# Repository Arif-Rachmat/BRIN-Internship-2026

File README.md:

<div align=center>
<table width="100%">
  <tr>
    <td width="25%" align="center">
      
    </td>
    <td width="50%" align="center">
      <h1>BRIN Internship - 2026</h1>
      <h3>Embedded Electronic Systems</h3>
    </td>
    <td width="25%"></td>
  </tr>
</table>

A collection of technical work, experiments, notes, and deliverables developed throughout my internship at **BRIN**.

</div>

---

## 🧭 Navigation

This repository is organized into individual workspaces assign to different branch, each containing the relevant implementation, documentation, experiments, and supporting files.

## Download / Cloning

To download or clone a specific branch, use this command:

```shell
git clone --branch=<branch-name> https://github.com/Arif-Rachmat/BRIN-Internship-2026.git <output-directory>
```

<!-- ASSIGNMENTS:START -->

### 📚 Index

1. Circuit/Electronics Design
   * [Basic #0: Adjustable Linear Power Supply](https://github.com/Arif-Rachmat/BRIN-Internship-2026/tree/Circuit-Basic-0-AdjLinearSupply)
   * [Intermediate #1: ATmega16–STM32BluePill Breakout/Adapter](https://github.com/Arif-Rachmat/BRIN-Internship-2026/tree/Circuit-Intermediate-1-ATmega16-STM32BP-Adapter)
   * [Capstone #0: Raspberry PI Dev Board](https://github.com/Arif-Rachmat/BRIN-Internship-2026/tree/Circuit-Capstone-0-RasPiDevBoard)
   * [Capstone #1: Tomography Switch Board Matrix](https://github.com/Arif-Rachmat/BRIN-Internship-2026/tree/Circuit-Capstone-1-TomographySwitchBoard)
     * [Capstone #1.1: TomographySwitchBoardV2](https://github.com/Arif-Rachmat/BRIN-Internship-2026/tree/Circuit-Capstone-1.1-TomographySwitchBoardV2main)
2. Embedded Programming
   * [Basic #0: Non-Blocking Blinky](https://github.com/Arif-Rachmat/BRIN-Internship-2026/tree/Embedded-Basic-0-NonBlocking-Blinky)
   * [Basic #1: UART](https://github.com/Arif-Rachmat/BRIN-Internship-2026/tree/Embedded-Basic-1-UART)
   * [Basic #2: ADC](https://github.com/Arif-Rachmat/BRIN-Internship-2026/tree/Embedded-Basic-2-ADC)
   * [Intermediate #1: I2C - LCD w/ PCF8574](https://github.com/Arif-Rachmat/BRIN-Internship-2026/tree/Circuit-Intermediate-1-I2C)
   * [Intermediate #3: 1-Wire DS18B20 Temperature Sensor](https://github.com/Arif-Rachmat/BRIN-Internship-2026/tree/Circuit-Intermediate-3-Onewire-DS18b20)

<!-- ASSIGNMENTS:END -->

---

<p align="center">
  <sub>Maintained as a personal technical workspace during my internship at BRIN.</sub>
</p>

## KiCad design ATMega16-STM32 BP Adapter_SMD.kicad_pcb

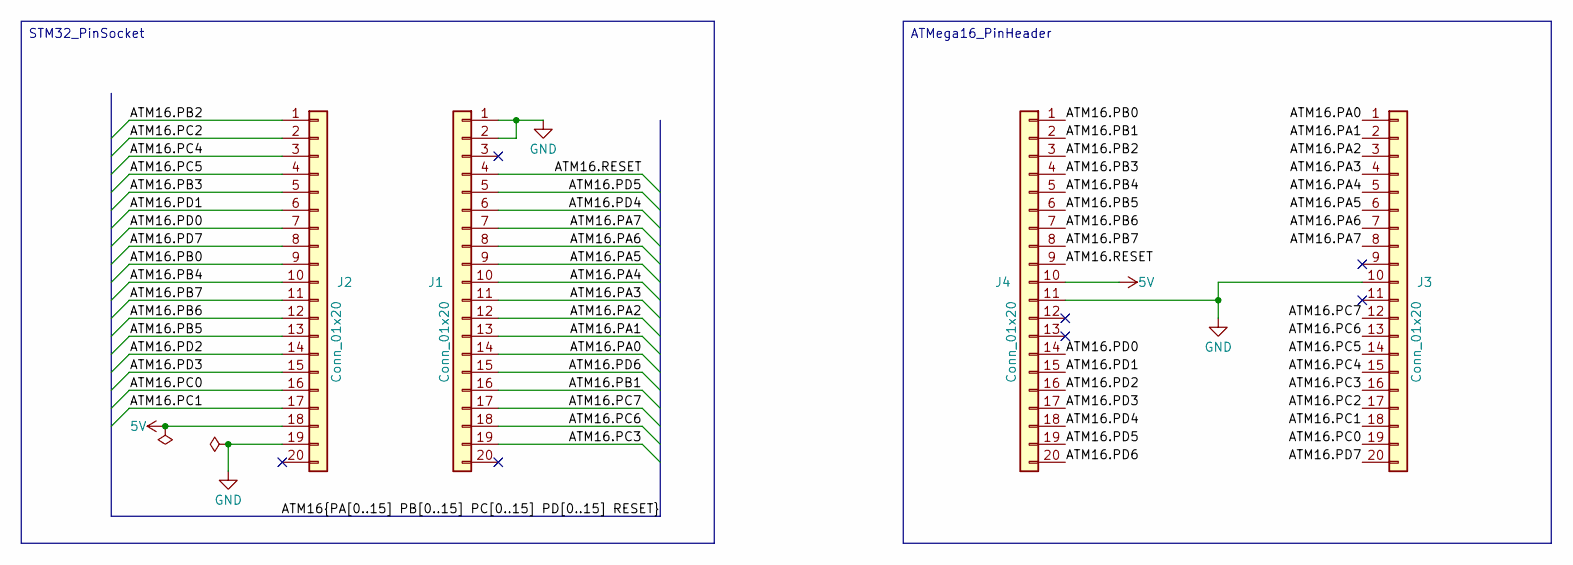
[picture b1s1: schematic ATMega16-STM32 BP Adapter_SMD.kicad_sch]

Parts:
J1: Conn_01x20; PinSocket_1x20_P2.54mm_Vertical_SMD_Pin1Right
J2: Conn_01x20; PinSocket_1x20_P2.54mm_Vertical_SMD_Pin1Left
J3: Conn_01x20; PinHeader_1x20_P2.54mm_Vertical_SMD_Pin1Right
J4: Conn_01x20; PinHeader_1x20_P2.54mm_Vertical_SMD_Pin1Left

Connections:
5V: J2.18, J4.10
/ATM16.PA0: J1.14, J3.1
/ATM16.PA1: J1.13, J3.2
/ATM16.PA2: J1.12, J3.3
/ATM16.PA3: J1.11, J3.4
/ATM16.PA4: J1.10, J3.5
/ATM16.PA5: J1.9, J3.6
/ATM16.PA6: J1.8, J3.7
/ATM16.PA7: J1.7, J3.8
/ATM16.PB0: J2.9, J4.1
/ATM16.PB1: J1.16, J4.2
/ATM16.PB2: J2.1, J4.3
/ATM16.PB3: J2.5, J4.4
/ATM16.PB4: J2.10, J4.5
/ATM16.PB5: J2.13, J4.6
/ATM16.PB6: J2.12, J4.7
/ATM16.PB7: J2.11, J4.8
/ATM16.PC0: J2.16, J3.19
/ATM16.PC1: J2.17, J3.18
/ATM16.PC2: J2.2, J3.17
/ATM16.PC3: J1.19, J3.16
/ATM16.PC4: J2.3, J3.15
/ATM16.PC5: J2.4, J3.14
/ATM16.PC6: J1.18, J3.13
/ATM16.PC7: J1.17, J3.12
/ATM16.PD0: J2.7, J4.14
/ATM16.PD1: J2.6, J4.15
/ATM16.PD2: J2.14, J4.16
/ATM16.PD3: J2.15, J4.17
/ATM16.PD4: J1.6, J4.18
/ATM16.PD5: J1.5, J4.19
/ATM16.PD6: J1.15, J4.20
/ATM16.PD7: J2.8, J3.20
/ATM16.RESET: J1.4, J4.9
GND: J1.1, J1.2, J2.19, J3.10, J4.11

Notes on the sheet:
ATMega16_PinHeader
STM32_PinSocket

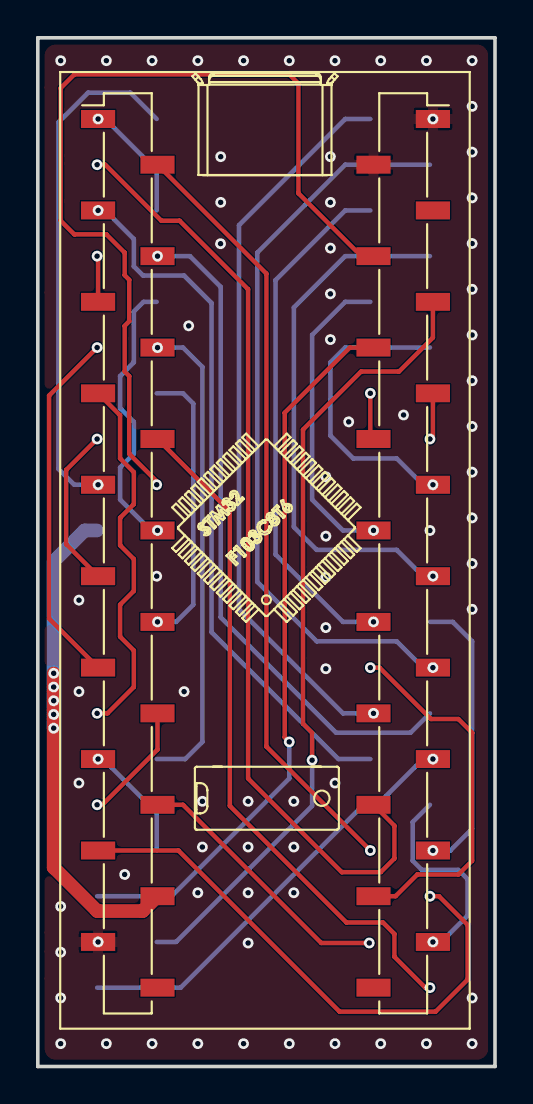
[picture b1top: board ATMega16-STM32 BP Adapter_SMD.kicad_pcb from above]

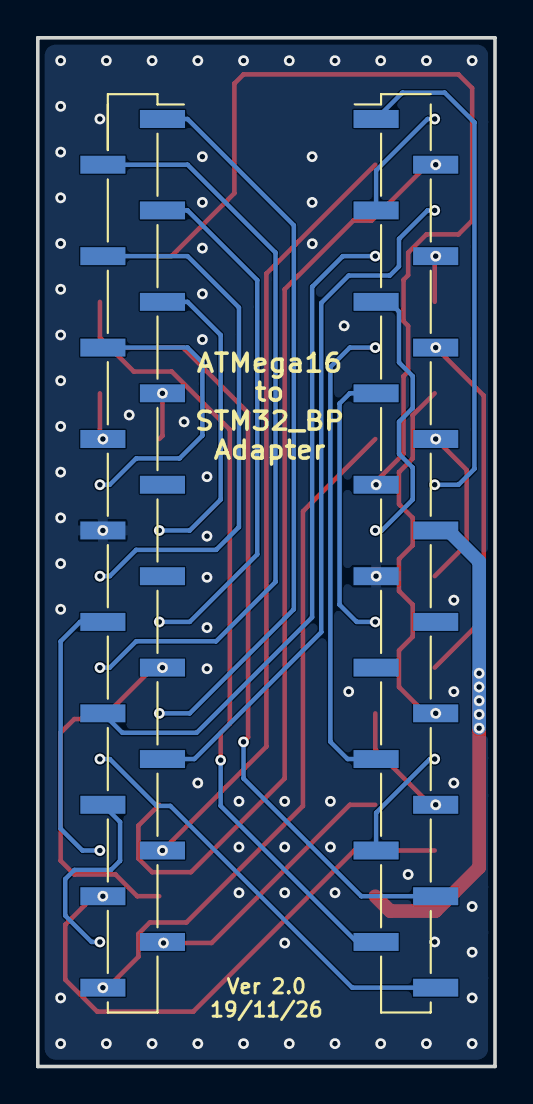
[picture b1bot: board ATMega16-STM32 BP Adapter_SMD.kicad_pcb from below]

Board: 2 copper layers, 25.4 x 57.1 mm, 5 parts (2 on the bottom side), 35 nets.

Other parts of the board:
U2: YAAJ_BluePill_Part_Like; BLUEPILL_SILKSCREEN

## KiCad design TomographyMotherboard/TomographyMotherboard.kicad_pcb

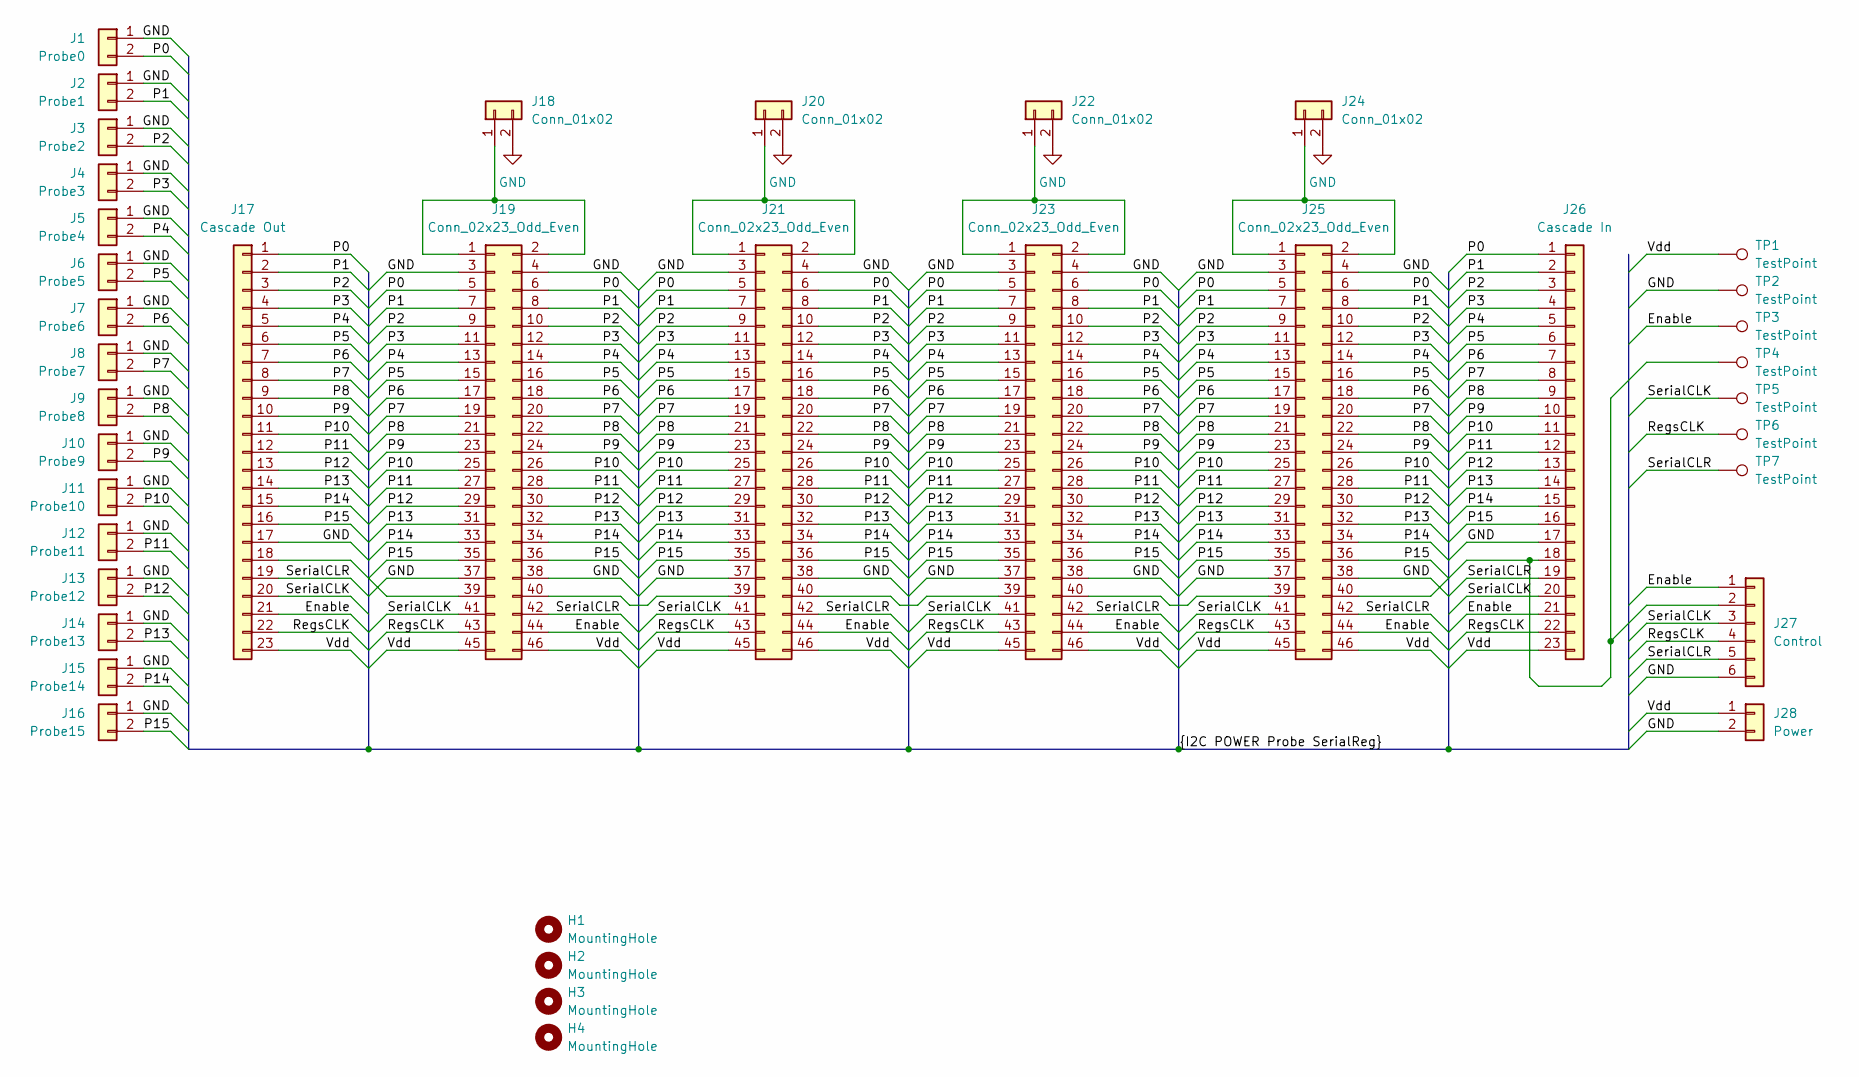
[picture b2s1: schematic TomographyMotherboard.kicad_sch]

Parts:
H1, H2, H3, H4: MountingHole; MountingHole_3.2mm_M3
J1: Probe0; Molex_KK-254_AE-6410-02A_1x02_P2.54mm_Vertical
J2: Probe1; Molex_KK-254_AE-6410-02A_1x02_P2.54mm_Vertical
J3: Probe2; Molex_KK-254_AE-6410-02A_1x02_P2.54mm_Vertical
J4: Probe3; Molex_KK-254_AE-6410-02A_1x02_P2.54mm_Vertical
J5: Probe4; Molex_KK-254_AE-6410-02A_1x02_P2.54mm_Vertical
J6: Probe5; Molex_KK-254_AE-6410-02A_1x02_P2.54mm_Vertical
J7: Probe6; Molex_KK-254_AE-6410-02A_1x02_P2.54mm_Vertical
J8: Probe7; Molex_KK-254_AE-6410-02A_1x02_P2.54mm_Vertical
J9: Probe8; Molex_KK-254_AE-6410-02A_1x02_P2.54mm_Vertical
J10: Probe9; Molex_KK-254_AE-6410-02A_1x02_P2.54mm_Vertical
J11: Probe10; Molex_KK-254_AE-6410-02A_1x02_P2.54mm_Vertical
J12: Probe11; Molex_KK-254_AE-6410-02A_1x02_P2.54mm_Vertical
J13: Probe12; Molex_KK-254_AE-6410-02A_1x02_P2.54mm_Vertical
J14: Probe13; Molex_KK-254_AE-6410-02A_1x02_P2.54mm_Vertical
J15: Probe14; Molex_KK-254_AE-6410-02A_1x02_P2.54mm_Vertical
J16: Probe15; Molex_KK-254_AE-6410-02A_1x02_P2.54mm_Vertical
J17: Cascade Out; PinHeader_1x23_P2.54mm_Horizontal
J18, J20, J22, J24: Conn_01x02; Molex_KK-254_AE-6410-02A_1x02_P2.54mm_Vertical
J19, J21, J23, J25: Conn_02x23_Odd_Even; PinSocket_2x23_P2.54mm_Vertical
J26: Cascade In; PinSocket_1x23_P2.54mm_Horizontal
J27: Control; Molex_KK-254_AE-6410-06A_1x06_P2.54mm_Vertical
J28: Power; Molex_KK-254_AE-6410-02A_1x02_P2.54mm_Vertical
TP1, TP2, TP3, TP4, TP5, TP6, TP7: TestPoint; TestPoint_Loop_D2.54mm_Drill1.5mm_Beaded

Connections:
/Enable: J17.21, J19.44, J21.44, J23.44, J25.44, J26.21, J27.1, TP3.1 (1_1)
/P0: J1.2, J17.1, J19.5, J19.6, J21.5, J21.6, J23.5, J23.6, J25.5, J25.6, J26.1
/P1: J2.2, J17.2, J19.7, J19.8, J21.7, J21.8, J23.7, J23.8, J25.7, J25.8, J26.2
/P2: J3.2, J17.3, J19.9, J19.10, J21.9, J21.10, J23.9, J23.10, J25.9, J25.10, J26.3
/P3: J4.2, J17.4, J19.11, J19.12, J21.11, J21.12, J23.11, J23.12, J25.11, J25.12, J26.4
/P4: J5.2, J17.5, J19.13, J19.14, J21.13, J21.14, J23.13, J23.14, J25.13, J25.14, J26.5
/P5: J6.2, J17.6, J19.15, J19.16, J21.15, J21.16, J23.15, J23.16, J25.15, J25.16, J26.6
/P6: J7.2, J17.7, J19.17, J19.18, J21.17, J21.18, J23.17, J23.18, J25.17, J25.18, J26.7
/P7: J8.2, J17.8, J19.19, J19.20, J21.19, J21.20, J23.19, J23.20, J25.19, J25.20, J26.8
/P8: J9.2, J17.9, J19.21, J19.22, J21.21, J21.22, J23.21, J23.22, J25.21, J25.22, J26.9
/P9: J10.2, J17.10, J19.23, J19.24, J21.23, J21.24, J23.23, J23.24, J25.23, J25.24, J26.10
/P10: J11.2, J17.11, J19.25, J19.26, J21.25, J21.26, J23.25, J23.26, J25.25, J25.26, J26.11
/P11: J12.2, J17.12, J19.27, J19.28, J21.27, J21.28, J23.27, J23.28, J25.27, J25.28, J26.12
/P12: J13.2, J17.13, J19.29, J19.30, J21.29, J21.30, J23.29, J23.30, J25.29, J25.30, J26.13
/P13: J14.2, J17.14, J19.31, J19.32, J21.31, J21.32, J23.31, J23.32, J25.31, J25.32, J26.14
/P14: J15.2, J17.15, J19.33, J19.34, J21.33, J21.34, J23.33, J23.34, J25.33, J25.34, J26.15
/P15: J16.2, J17.16, J19.35, J19.36, J21.35, J21.36, J23.35, J23.36, J25.35, J25.36, J26.16
/RegsCLK: J17.22, J19.43, J21.43, J23.43, J25.43, J26.22, J27.4, TP6.1 (1_1)
/SerialCLK: J17.20, J19.41, J21.41, J23.41, J25.41, J26.20, J27.3, TP5.1 (1_1)
/SerialCLR: J17.19, J19.42, J21.42, J23.42, J25.42, J26.19, J27.5, TP7.1 (1_1)
/Vdd: J17.23, J19.45, J19.46, J21.45, J21.46, J23.45, J23.46, J25.45, J25.46, J26.23, J28.1, TP1.1 (1_1)
GND: J1.1, J2.1, J3.1, J4.1, J5.1, J6.1, J7.1, J8.1, J9.1, J10.1, J11.1, J12.1, J13.1, J14.1, J15.1, J16.1, J17.17, J18.2, J19.3, J19.4, J19.37, J19.38, J20.2, J21.3, J21.4, J21.37, J21.38, J22.2, J23.3, J23.4, J23.37, J23.38, J24.2, J25.3, J25.4, J25.37, J25.38, J26.17, J27.6, J28.2, TP2.1 (1_1)
unnamed: J17.18, J19.39
unnamed: J18.1, J19.1, J19.2
unnamed: J19.40, J21.39
unnamed: J20.1, J21.1, J21.2
unnamed: J21.40, J23.39
unnamed: J22.1, J23.1, J23.2
unnamed: J23.40, J25.39
unnamed: J24.1, J25.1, J25.2
unnamed: J25.40, J26.18, J27.2, TP4.1 (1_1)

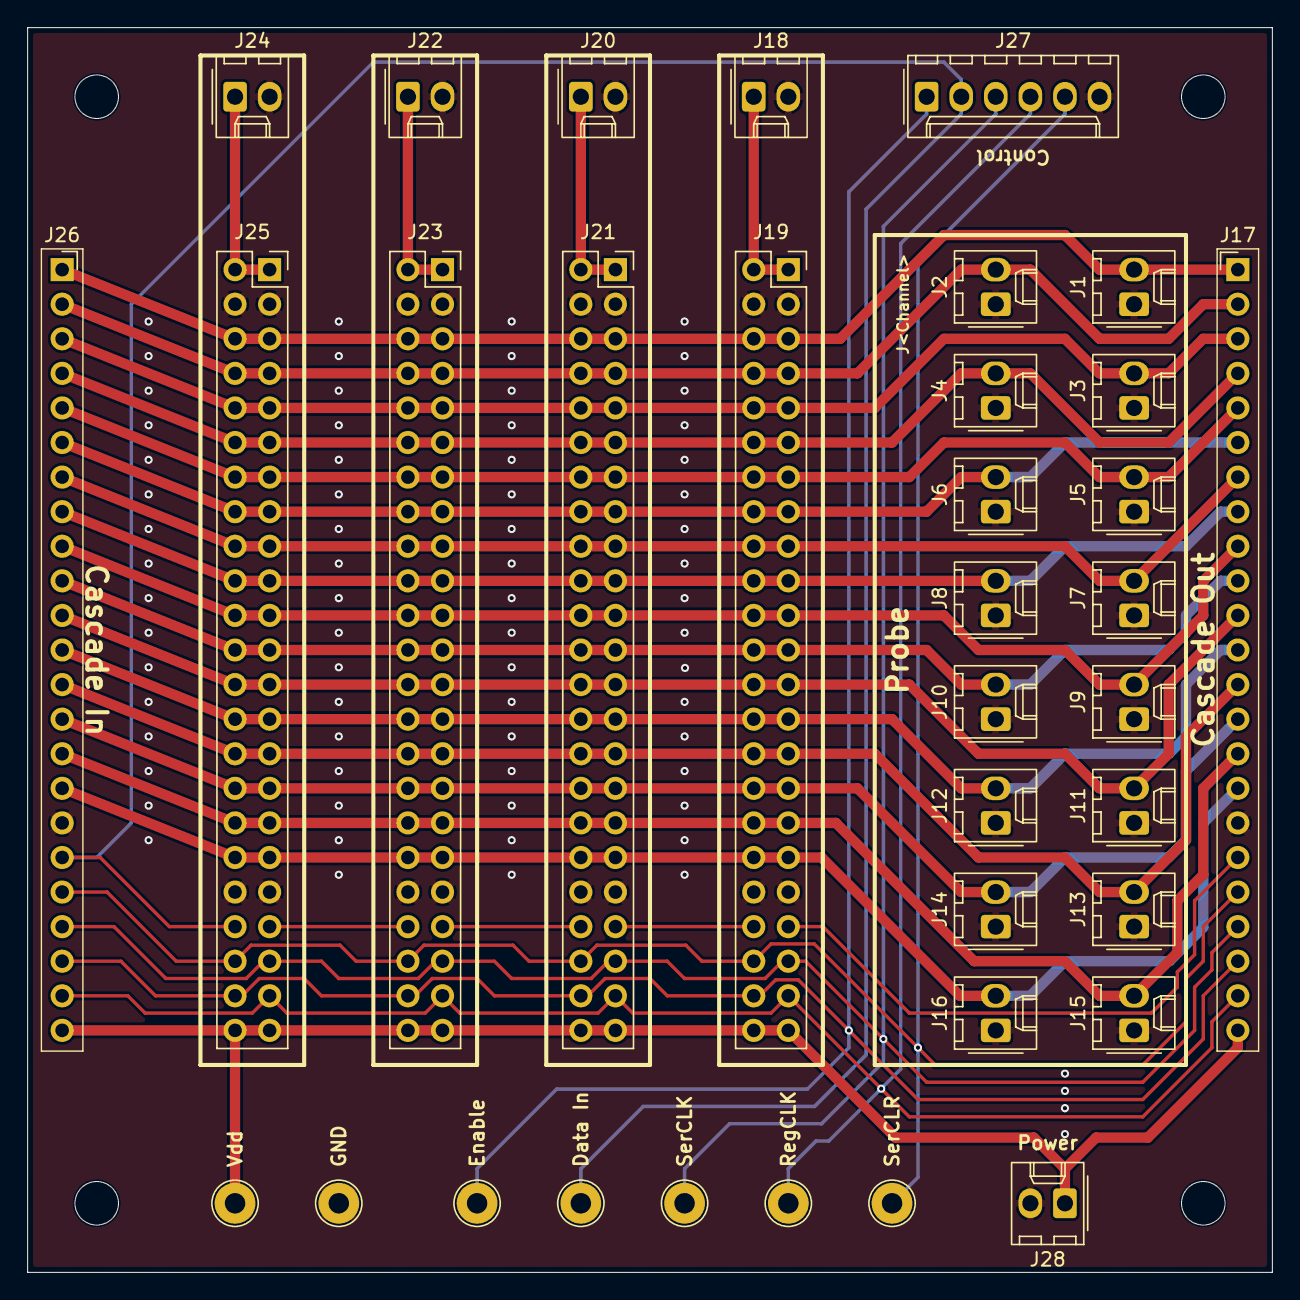
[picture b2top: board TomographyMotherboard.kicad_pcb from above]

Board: 2 copper layers, 91.4 x 91.4 mm, 39 parts (0 on the bottom side), 31 nets.

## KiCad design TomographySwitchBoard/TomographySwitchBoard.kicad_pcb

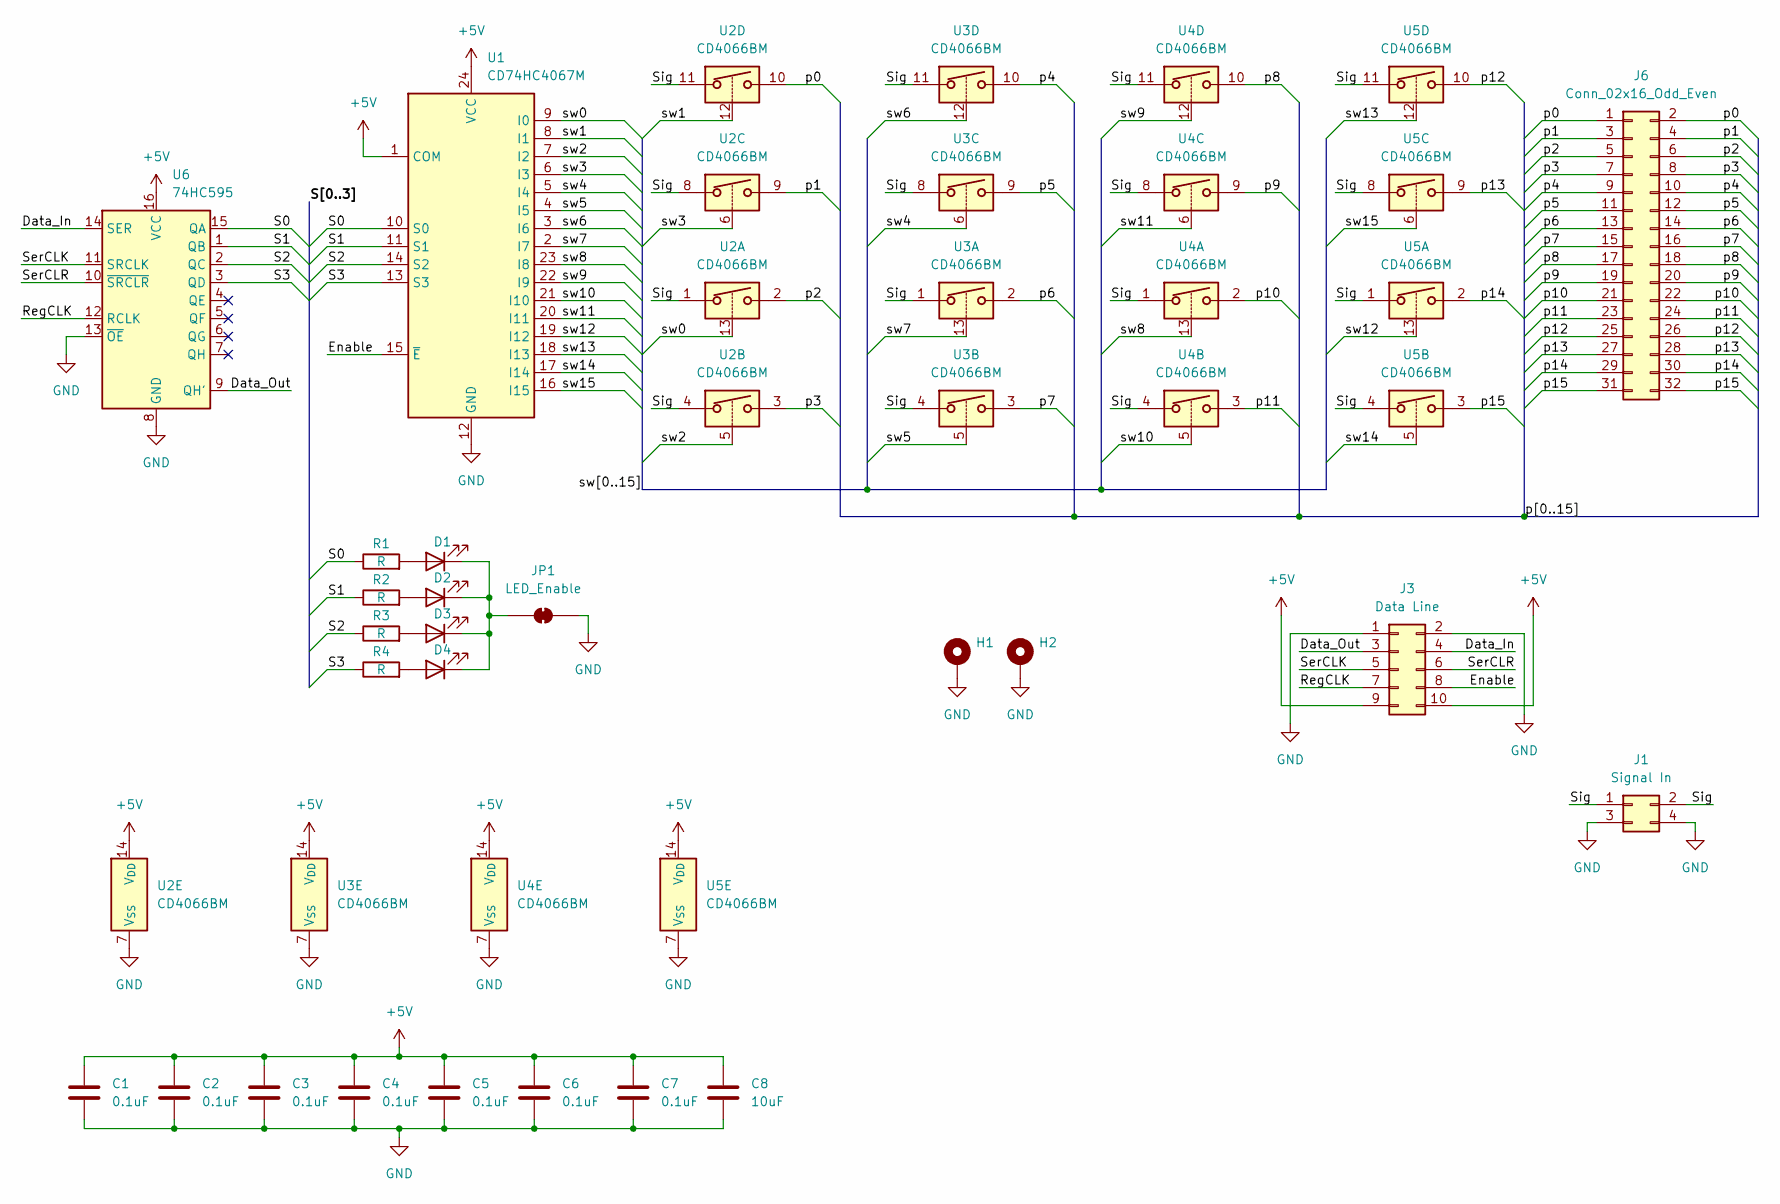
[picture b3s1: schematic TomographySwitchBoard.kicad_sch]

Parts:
C1, C2, C3, C4, C5, C6, C7: 0.1uF; C_0603_1608Metric
C8: 10uF; C_0603_1608Metric
D1, D2, D3, D4: LED; LED_0603_1608Metric
H1, H2: MountingHole_Pad; MountingHole_2.2mm_M2_Pad_Via
J1: Signal In; PinHeader_2x02_P2.54mm_Horizontal
J3: Data Line; PinHeader_2x05_P2.54mm_Horizontal
J6: Conn_02x16_Odd_Even; PinHeader_2x16_P2.54mm_Horizontal
JP1: LED_Enable; SolderJumper-2_P1.3mm_Bridged_Pad1.0x1.5mm
R1, R2, R3, R4: R; R_0603_1608Metric
U1: CD74HC4067M; SOIC-24W_7.5x15.4mm_P1.27mm
U2, U3, U4, U5: CD4066BM; SOIC-14_3.9x8.7mm_P1.27mm
U6: 74HC595; SOIC-16_3.9x9.9mm_P1.27mm

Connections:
+5V: C1.1, C2.1, C3.1, C4.1, C5.1, C6.1, C7.1, C8.1, J3.9, J3.10, U1.1 (COM), U1.24 (VCC), U2.14 (V_{DD}), U3.14 (V_{DD}), U4.14 (V_{DD}), U5.14 (V_{DD}), U6.16 (VCC)
/Data_In: J3.4, U6.14 (SER)
/Data_Out: J3.3, U6.9 (QH')
/Enable: J3.8, U1.15 (~E)
/RegCLK: J3.7, U6.12 (RCLK)
/S0: R1.1, U1.10 (S0), U6.15 (QA)
/S1: R2.1, U1.11 (S1), U6.1 (QB)
/S2: R3.1, U1.14 (S2), U6.2 (QC)
/S3: R4.1, U1.13 (S3), U6.3 (QD)
/SerCLK: J3.5, U6.11 (SRCLK)
/SerCLR: J3.6, U6.10 (~SRCLR)
/Sig: J1.1, J1.2, U2.1, U2.4, U2.8, U2.11, U3.1, U3.4, U3.8, U3.11, U4.1, U4.4, U4.8, U4.11, U5.1, U5.4, U5.8, U5.11
/p0: J6.1, J6.2, U2.10
/p1: J6.3, J6.4, U2.9
/p2: J6.5, J6.6, U2.2
/p3: J6.7, J6.8, U2.3
/p4: J6.9, J6.10, U3.10
/p5: J6.11, J6.12, U3.9
/p6: J6.13, J6.14, U3.2
/p7: J6.15, J6.16, U3.3
/p8: J6.17, J6.18, U4.10
/p9: J6.19, J6.20, U4.9
/p10: J6.21, J6.22, U4.2
/p11: J6.23, J6.24, U4.3
/p12: J6.25, J6.26, U5.10
/p13: J6.27, J6.28, U5.9
/p14: J6.29, J6.30, U5.2
/p15: J6.31, J6.32, U5.3
/sw0: U1.9 (I0), U2.13
/sw1: U1.8 (I1), U2.12
/sw2: U1.7 (I2), U2.5
/sw3: U1.6 (I3), U2.6
/sw4: U1.5 (I4), U3.6
/sw5: U1.4 (I5), U3.5
/sw6: U1.3 (I6), U3.12
/sw7: U1.2 (I7), U3.13
/sw8: U1.23 (I8), U4.13
/sw9: U1.22 (I9), U4.12
/sw10: U1.21 (I10), U4.5
/sw11: U1.20 (I11), U4.6
/sw12: U1.19 (I12), U5.13
/sw13: U1.18 (I13), U5.12
/sw14: U1.17 (I14), U5.5
/sw15: U1.16 (I15), U5.6
GND: C1.2, C2.2, C3.2, C4.2, C5.2, C6.2, C7.2, C8.2, H1.1 (1_1), H2.1 (1_1), J1.3, J1.4, J3.1, J3.2, JP1.2 (B), U1.12 (GND), U2.7 (V_{SS}), U3.7 (V_{SS}), U4.7 (V_{SS}), U5.7 (V_{SS}), U6.8 (GND), U6.13 (~OE)
unnamed: D1.2 (A), R1.2
unnamed: D1.1 (K), D2.1 (K), D3.1 (K), D4.1 (K), JP1.1 (A)
unnamed: D2.2 (A), R2.2
unnamed: D3.2 (A), R3.2
unnamed: D4.2 (A), R4.2

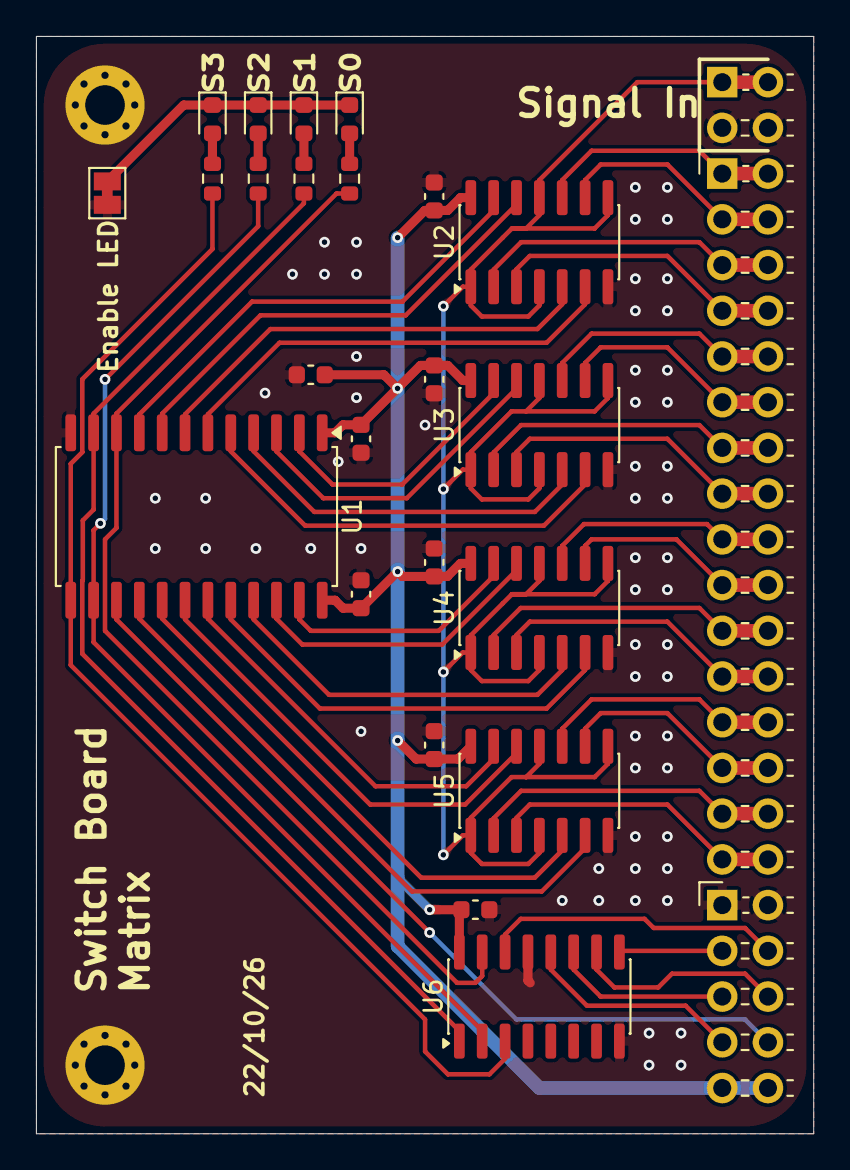
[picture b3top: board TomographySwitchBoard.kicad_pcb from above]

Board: 2 copper layers, 43.2 x 61.0 mm, 28 parts (0 on the bottom side), 50 nets.

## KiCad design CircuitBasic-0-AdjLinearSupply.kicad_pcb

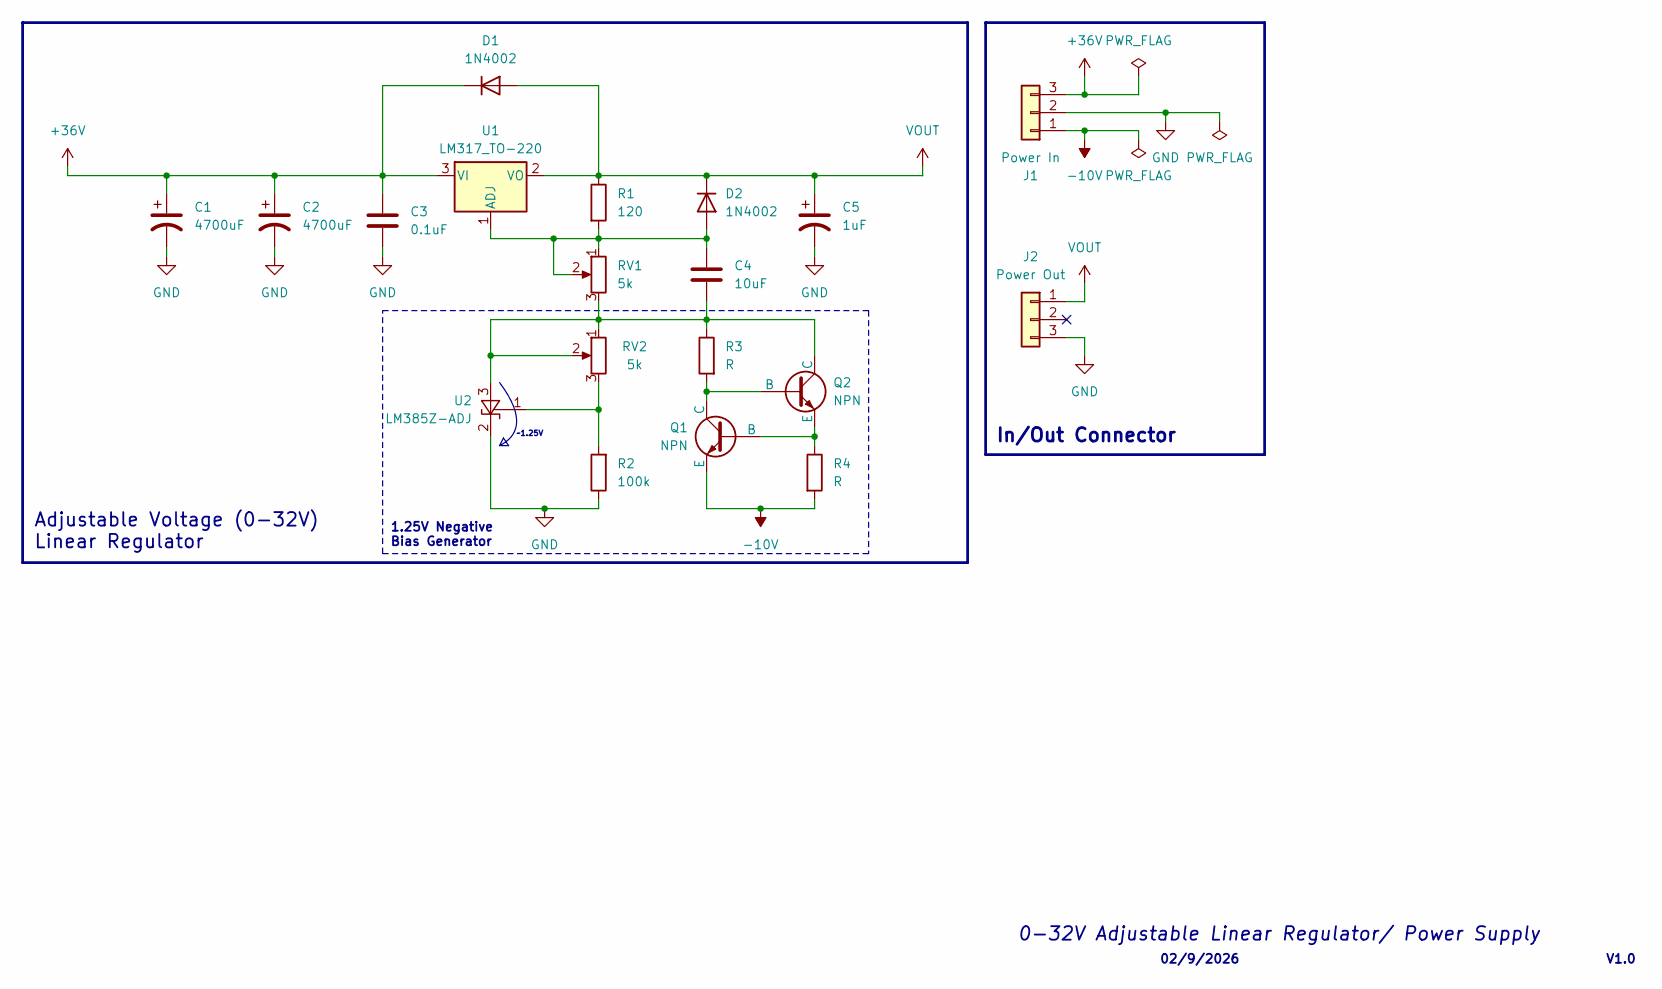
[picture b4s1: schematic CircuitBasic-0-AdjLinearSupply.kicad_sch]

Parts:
C1, C2: 4700uF; CP_Radial_D18.0mm_P7.50mm
C3: 0.1uF; C_Disc_D5.1mm_W3.2mm_P5.00mm
C4: 10uF; C_Disc_D5.1mm_W3.2mm_P5.00mm
C5: 1uF; CP_Radial_D5.0mm_P2.00mm
D1, D2: 1N4002; D_DO-41_SOD81_P10.16mm_Horizontal
J1: Power In; FanPinHeader_1x03_P2.54mm_Vertical
J2: Power Out; FanPinHeader_1x03_P2.54mm_Vertical
Q1, Q2: NPN; TO-92_Inline
R1: 120; R_Axial_DIN0207_L6.3mm_D2.5mm_P10.16mm_Horizontal
R2: 100k; R_Axial_DIN0207_L6.3mm_D2.5mm_P10.16mm_Horizontal
R3, R4: R; R_Axial_DIN0207_L6.3mm_D2.5mm_P10.16mm_Horizontal
RV1, RV2: 5k; Potentiometer_Bourns_3296W_Vertical
U1: LM317_TO-220; TO-220-3_Vertical
U2: LM385Z-ADJ; TO-92_Inline

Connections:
+36V: C1.1, C2.1, C3.1, D1.1 (K), J1.3, U1.3 (VI)
-10V: J1.1, Q1.3 (E), R4.2
GND: C1.2, C2.2, C3.2, C5.2, J1.2, J2.3, R2.1, U2.2 (K)
unnamed: C4.1, D2.2 (A), R1.2, RV1.1, RV1.2, U1.1 (ADJ)
unnamed: Q1.2 (B), Q2.3 (E), R4.1
unnamed: Q1.1 (C), Q2.2 (B), R3.2
unnamed: C4.2, Q2.1 (C), R3.1, RV1.3, RV2.1, RV2.2, U2.3 (A)
unnamed: R2.2, RV2.3, U2.1 (FB)
VOUT: C5.1, D1.2 (A), D2.1 (K), J2.1, R1.1, U1.2 (VO)

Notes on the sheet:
1.25V Negative Bias Generator
0-32V Adjustable Linear Regulator/ Power Supply
V1.0
~1.25V
02/9/2026
In/Out Connector
Adjustable Voltage (0-32V) Linear Regulator

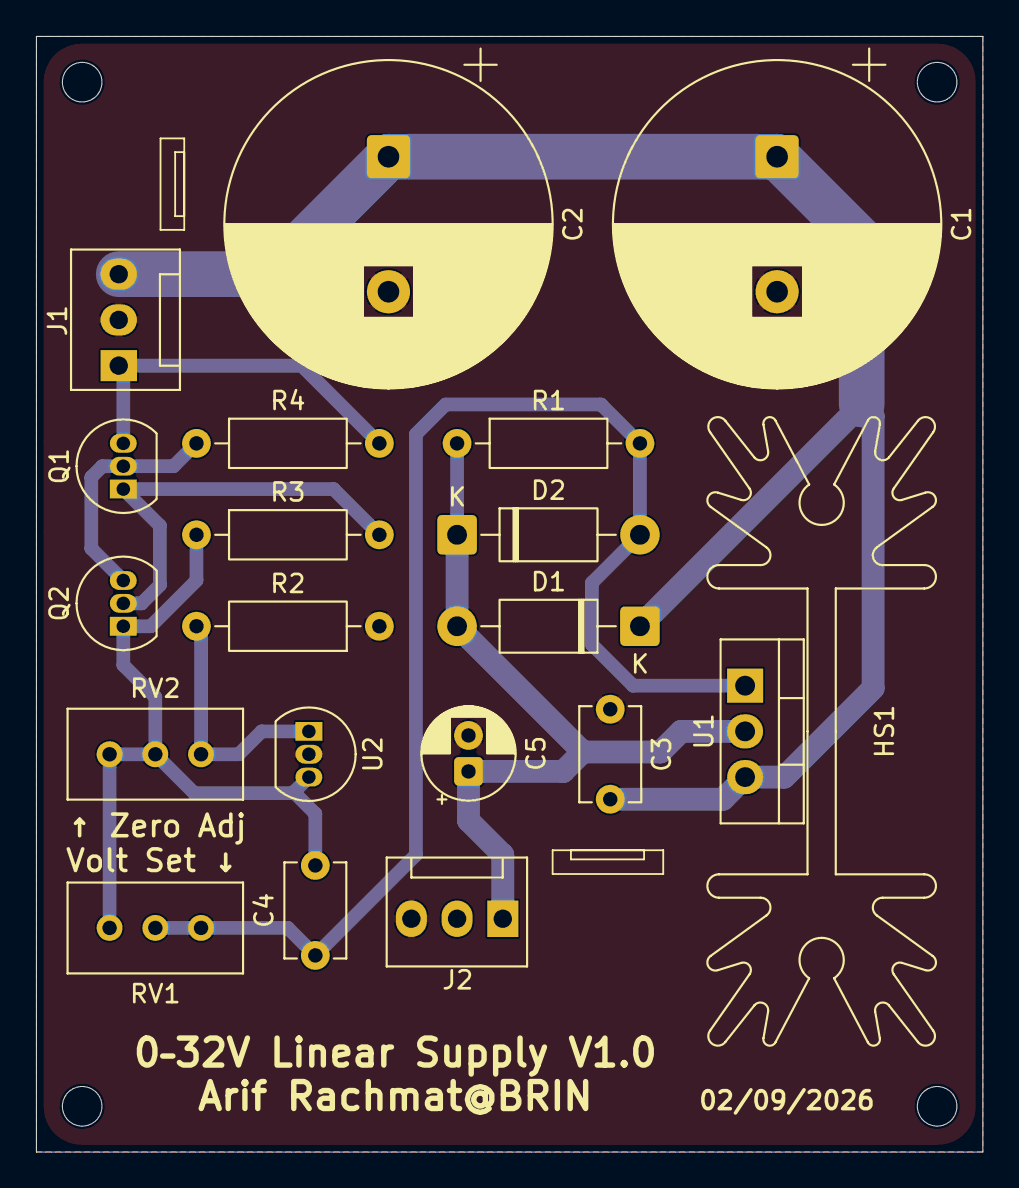
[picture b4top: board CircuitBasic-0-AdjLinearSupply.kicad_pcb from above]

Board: 2 copper layers, 52.6 x 62.0 mm, 20 parts (0 on the bottom side), 9 nets.

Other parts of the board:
HS1: Heatsink_AAVID_Extruded_531002B00000G_34.9x12.7mm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; Heatsink_AAVID_Extruded_531002B00000G_34.9x12.7mm_H25.4mm
